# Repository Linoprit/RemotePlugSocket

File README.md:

# RemotePlugSocket
Plug Socket, that can be controlled by Mqtt-Messages. Especially designed for HomeAssistant.

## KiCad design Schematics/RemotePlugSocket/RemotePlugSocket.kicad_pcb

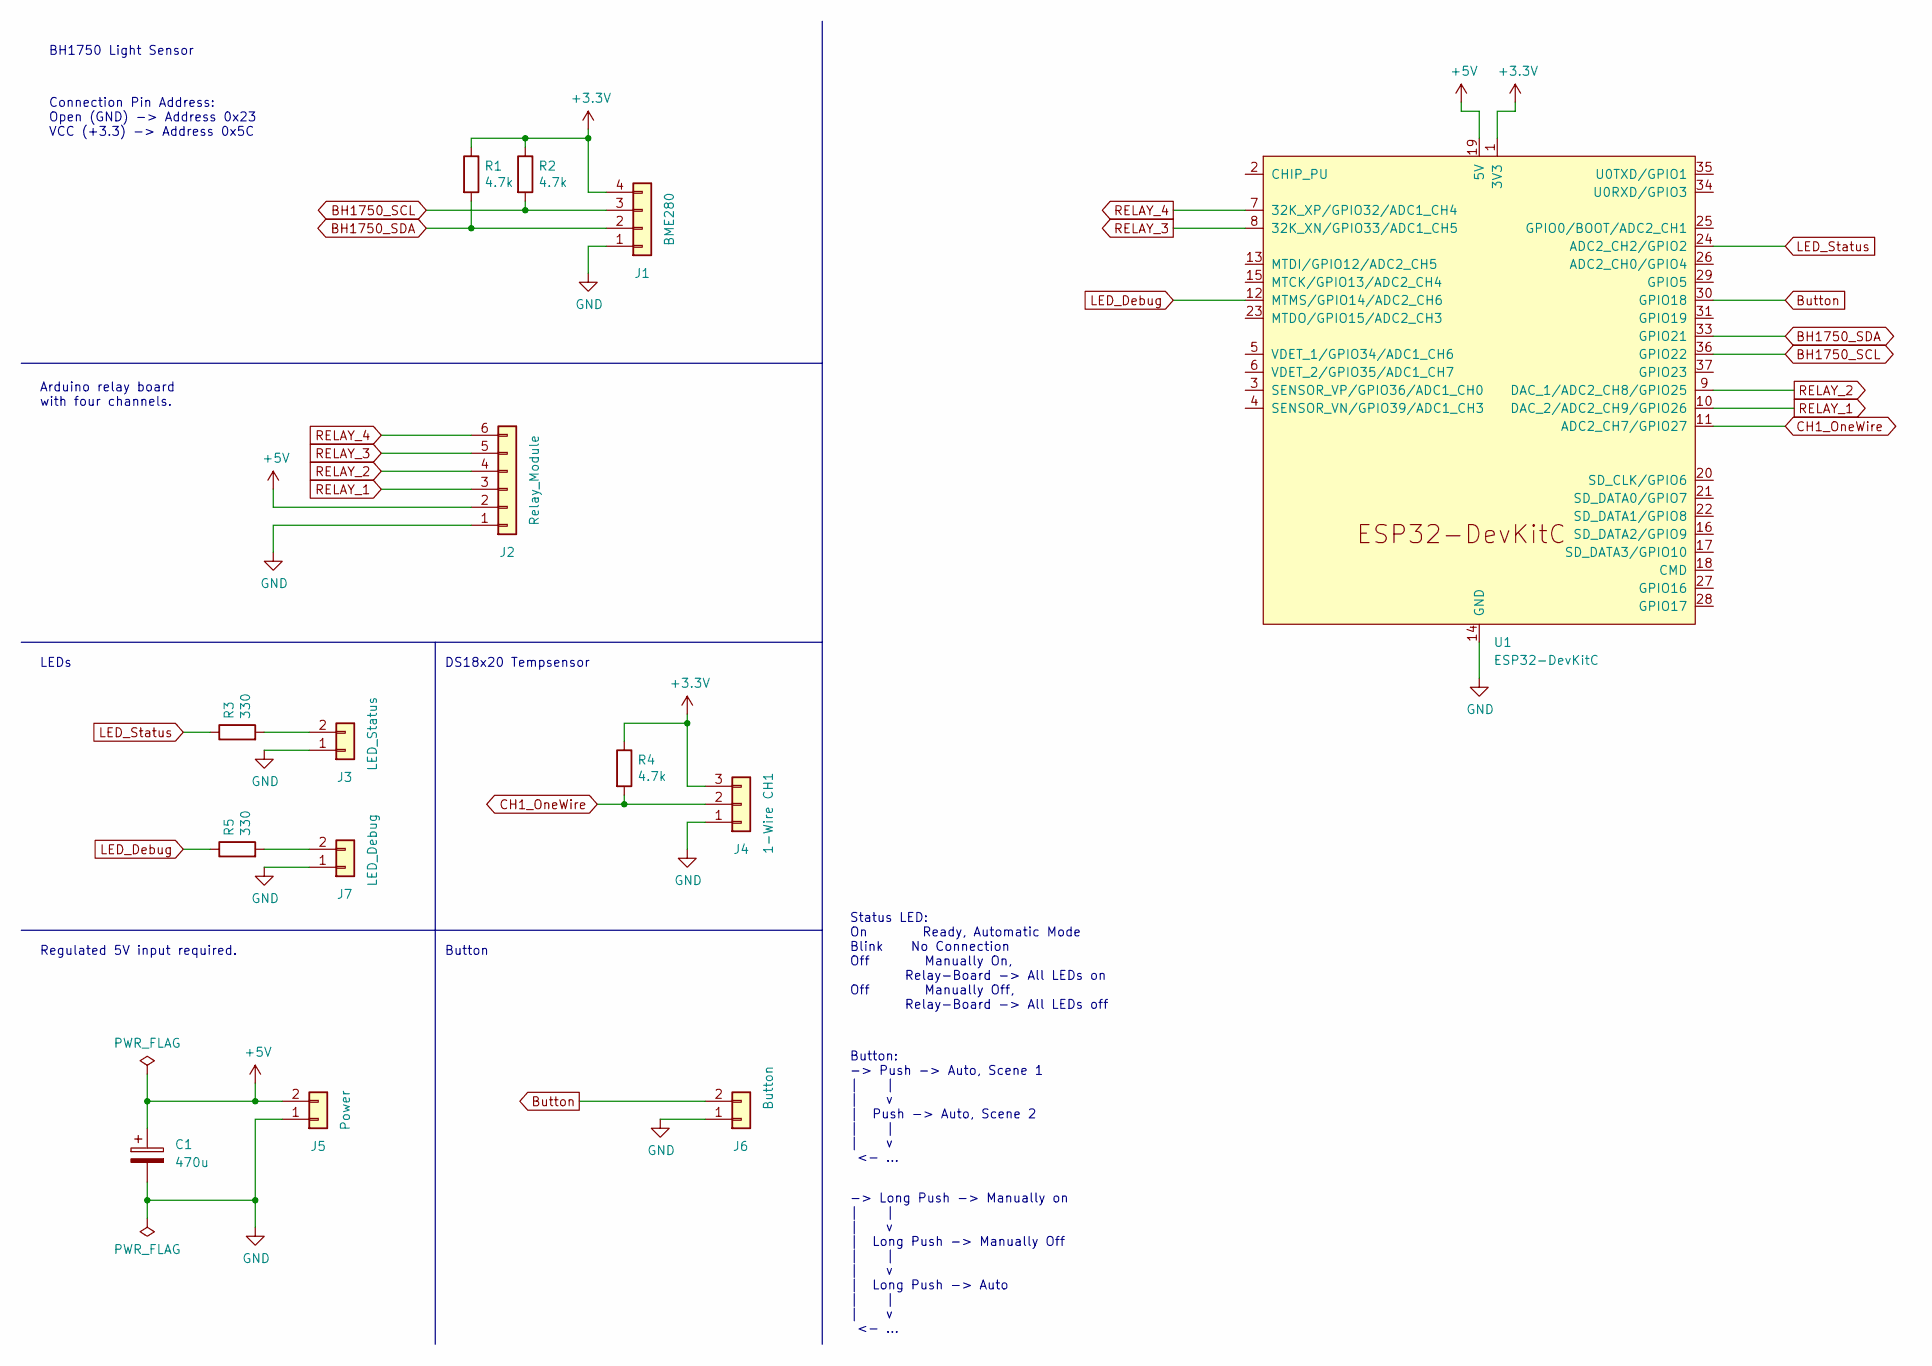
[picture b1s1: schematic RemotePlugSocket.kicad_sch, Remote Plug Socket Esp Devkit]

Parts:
C1: 470u; CP_Radial_D8.0mm_P3.50mm
J1: BME280; Molex_KK-254_AE-6410-04A_1x04_P2.54mm_Vertical
J2: Relay_Module; Molex_KK-254_AE-6410-06A_1x06_P2.54mm_Vertical
J3: LED_Status; Molex_KK-254_AE-6410-02A_1x02_P2.54mm_Vertical
J4: 1-Wire CH1; Molex_KK-254_AE-6410-03A_1x03_P2.54mm_Vertical
J5: Power; Molex_KK-254_AE-6410-02A_1x02_P2.54mm_Vertical
J6: Button; Molex_KK-254_AE-6410-02A_1x02_P2.54mm_Vertical
J7: LED_Debug; Molex_KK-254_AE-6410-02A_1x02_P2.54mm_Vertical
R1, R2, R4: 4.7k; R_Axial_DIN0207_L6.3mm_D2.5mm_P7.62mm_Horizontal
R3, R5: 330; R_Axial_DIN0207_L6.3mm_D2.5mm_P7.62mm_Horizontal
U1: ESP32-DevKitC

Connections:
+3V3: J1.4, J4.3, R1.1, R2.1, R4.1, U1.1 (3V3)
+5V: C1.1, J2.2, J5.2, U1.19 (5V)
BH1750_SCL: J1.3, R2.2, U1.36 (GPIO22)
BH1750_SDA: J1.2, R1.2, U1.33 (GPIO21)
Button: J6.2, U1.30 (GPIO18)
CH1_OneWire: J4.2, R4.2, U1.11 (ADC2_CH7/GPIO27)
GND: C1.2, J1.1, J2.1, J3.1, J4.1, J5.1, J6.1, J7.1, U1.14 (GND), U1.32 (GND), U1.38 (GND)
LED_Debug: R5.1, U1.12 (MTMS/GPIO14/ADC2_CH6)
LED_Status: R3.1, U1.24 (ADC2_CH2/GPIO2)
unnamed: J3.2, R3.2
unnamed: J7.2, R5.2
RELAY_1: J2.3, U1.10 (DAC_2/ADC2_CH9/GPIO26)
RELAY_2: J2.4, U1.9 (DAC_1/ADC2_CH8/GPIO25)
RELAY_3: J2.5, U1.8 (32K_XN/GPIO33/ADC1_CH5)
RELAY_4: J2.6, U1.7 (32K_XP/GPIO32/ADC1_CH4)

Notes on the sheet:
BH1750 Light Sensor
Status LED: On Ready, Automatic Mode Blink No Connection Off Manually On, Relay-Board -> All LEDs on Off Manually Off, Relay-Board -> All LEDs off
DS18x20 Tempsensor
Connection Pin Address: Open (GND) -> Address 0x23 VCC (+3.3) -> Address 0x5C
Button
LEDs
-> Long Push -> Manually on | | | v | Long Push -> Manually Off | | | v | Long Push -> Auto | | | v <- ...
Arduino relay board with four channels.
Regulated 5V input required.
Button: -> Push -> Auto, Scene 1 | | | v | Push -> Auto, Scene 2 | | | v <- ...

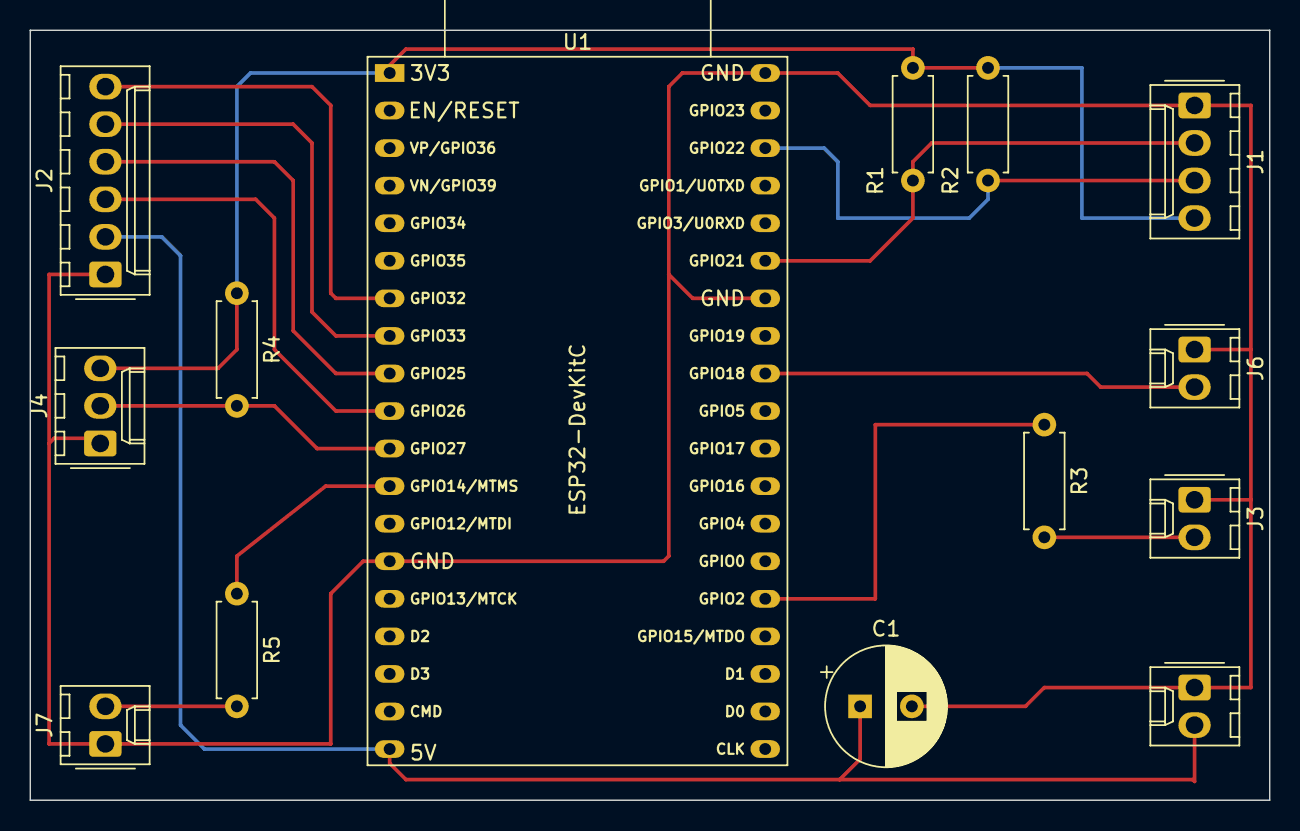
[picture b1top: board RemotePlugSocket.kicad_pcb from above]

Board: 2 copper layers, 83.8 x 52.1 mm, 14 parts (0 on the bottom side), 15 nets.

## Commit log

2024-11-17 initial
2024-11-24 Schematics: pinning of relays and oneWire changed. StateMachine added.
2024-11-30 Relay switching from HA now works.
2024-12-01 StateMachine now active
2024-12-08 Did some tweaks with sending availability of the switches.
